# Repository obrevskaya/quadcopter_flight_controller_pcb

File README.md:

# Разработка платы контроллера полёта квадрокоптера

## Описание проекта

Проект посвящён разработке печатной платы контроллера полёта квадрокоптера в системе автоматизированного проектирования KiCad.

В рамках работы были выполнены:

* разработка структурной схемы устройства;
* выбор и обоснование элементной базы;
* разработка принципиальной электрической схемы;
* трассировка двухслойной печатной платы;
* создание трёхмерной модели печатной платы;
* подготовка производственной документации для изготовления платы.

---

## Используемая элементная база

### Микроконтроллер

**STM32F405VGTx**

* ARM Cortex-M4;
* 32-разрядная архитектура;
* обработка данных датчиков;
* формирование управляющих сигналов.

### Датчики

**ICM-20602**

* трёхосевой гироскоп;
* трёхосевой акселерометр.

**LIS3MDL**

* трёхосевой магнитометр;
* определение ориентации относительно магнитного поля Земли.

**BMP280**

* барометрический датчик давления;
* оценка высоты полёта.

### Навигация

**NEO-M8N**

* GPS/GLONASS модуль;
* определение координат и скорости движения.

### Подсистема питания

**LM7805**

* стабилизатор питания 5 В.

**AMS1117-3.3**

* стабилизатор питания 3.3 В.

---

## Разработка печатной платы

Печатная плата выполнена в системе автоматизированного проектирования **KiCad**.

Особенности реализации:

* двухслойная конструкция;
* заливка полигона земли на обоих слоях;
* разделение сигнальных и силовых цепей;
* минимизация длины соединений;
* размещение монтажных отверстий;
* подготовка Gerber-файлов для производства.

Размер платы:

```text
70 × 70 мм
```
---

## Полученные результаты

В результате работы была разработана печатная плата контроллера полёта квадрокоптера, включающая:

* структурную схему устройства;
* принципиальную электрическую схему;
* двухслойную топологию печатной платы;
* комплект производственных файлов;
* трёхмерную модель устройства.

Полученная конструкция пригодна для последующего изготовления и монтажа компонентов.

---

## Используемые инструменты

* KiCad
* Draw.io
* ARM STM32
* PCB Design
* Embedded Systems

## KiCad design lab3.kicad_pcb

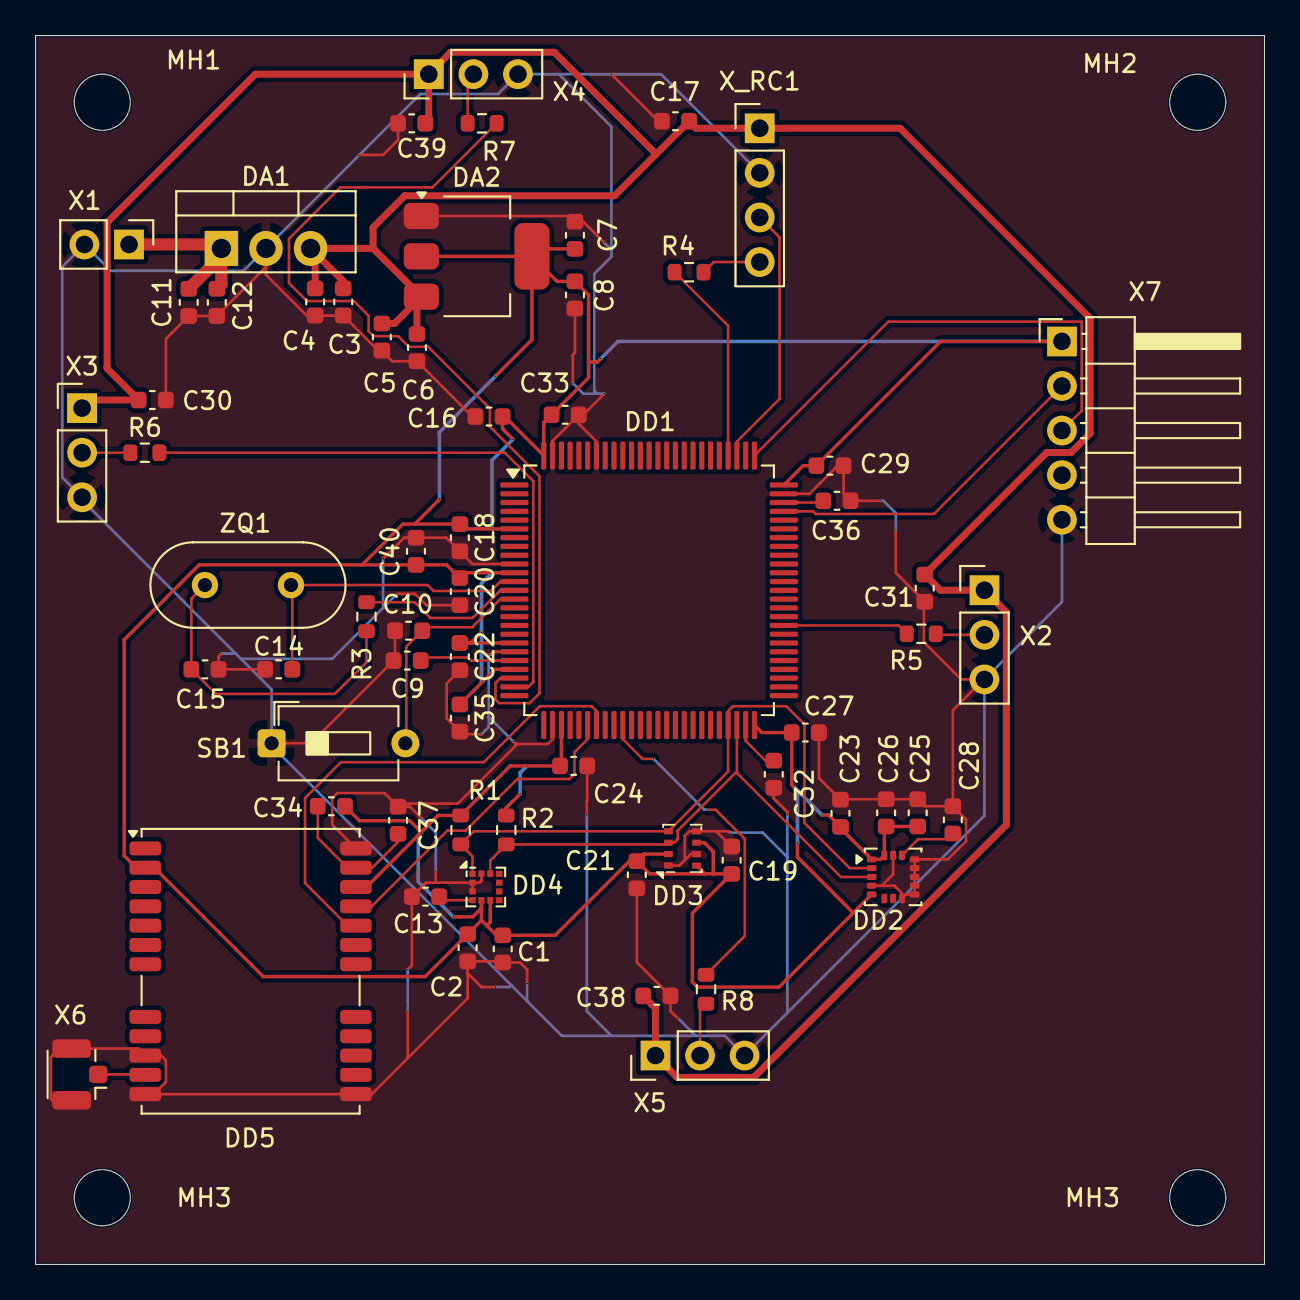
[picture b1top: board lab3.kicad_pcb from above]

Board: 2 copper layers, 70.0 x 70.0 mm, 69 parts (0 on the bottom side), 32 nets.

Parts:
C1, C3, C5, C8, C12, C13, C17, C18, C19, C20, C21, C22, C24, C25, C27, C28, C29, C30, C31, C33, C34, C35, C38, C39: 100nF; C_0603_1608Metric
C2: 1nF; C_0603_1608Metric
C4, C6, C7, C11: 10uF; C_0603_1608Metric
C9: 0.1uF; C_0603_1608Metric
C10, C16, C23: 10nF; C_0603_1608Metric
C14, C15: 30nF; C_0603_1608Metric
C26: 2.2 uF; C_0603_1608Metric
C32, C36: 2.2uF; C_0603_1608Metric
C37: 10 uF; C_0603_1608Metric
C40: 4.7uF; C_0603_1608Metric
DA1: LM7805_TO220; TO-220-3_Vertical
DA2: AMS1117-3.3; SOT-223-3_TabPin2
DD1: STM32F405VGTx; LQFP-100_14x14mm_P0.5mm
DD2: ICM-20602; LGA-16_3x3mm_P0.5mm_LayoutBorder3x5y
DD3: BMP280; Bosch_LGA-8_2x2.5mm_P0.65mm_ClockwisePinNumbering
DD4: LIS3MDL; LGA-12_2x2mm_P0.5mm
DD5: NEO-M8N; ublox_NEO
MH1, MH2, MH3, MH3#2: MountingHole_3.2mm_M3
R1, R2: 4.7k; R_0603_1608Metric
R3, R4: 100; R_0603_1608Metric
R5, R6, R7, R8: 100 Ω; R_0603_1608Metric
SB1: SW_Push; SW_DIP_SPSTx01_Slide_6.7x4.1mm_W7.62mm_P2.54mm_LowProfile
X1: Conn_01x02; PinHeader_1x02_P2.54mm_Vertical
X2, X3, X4, X5: Conn_01x03; PinHeader_1x03_P2.54mm_Vertical
X6: Conn_Coaxial; U.FL_Hirose_U.FL-R-SMT-1_Vertical
X7: Conn_01x05; PinHeader_1x05_P2.54mm_Horizontal
X_RC1: RC_RECEIVER; PinHeader_1x04_P2.54mm_Vertical
ZQ1: Crystal; Crystal_HC18-U_Vertical

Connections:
+3V3: C1.1, C2.2, C7.1, C8.1, C16.1, C18.1, C19.2, C20.1, C21.2, C22.1, C23.2, C24.1, C25.2, C26.2, C27.1, C29.1, C33.1, C34.2, C35.1, C40.2, DA2.2 (VO), DD1.6 (VBAT), DD1.11 (VDD), DD1.19 (VDD), DD1.22 (VDDA), DD1.28 (VDD), DD1.50 (VDD), DD1.75 (VDD), DD1.100 (VDD), DD2.1 (VDDIO), DD2.5 (~CS), DD2.16 (VDD), DD3.2 (CSB), DD3.6 (VDDIO), DD3.8 (VDD), DD4.5 (Vdd), DD4.6 (Vdd_IO), DD5.2 (D_SEL), DD5.22 (V_BCKP), R1.2, R2.1, X7.1
+5V: C3.1, C4.1, C5.1, C6.1, C17.1, C30.1, C31.1, C38.1, C39.1, DA1.3 (VO), DA2.3 (VI), X2.1, X3.1, X4.1, X5.1, X_RC1.1
+BATT: C11.1, C12.1, DA1.1 (VI), X1.1
GND: C1.2, C2.1, C3.2, C4.2, C5.2, C6.2, C7.2, C8.2, C9.2, C10.1, C11.2, C12.2, C13.1, C14.1, C15.1, C16.2, C17.2, C18.2, C19.1, C20.2, C21.1, C22.2, C23.1, C24.2, C25.1, C26.1, C27.2, C28.1, C29.2, C30.2, C31.2, C32.2, C33.2, C35.2, C36.2, C37.1, C38.2, C39.2, C40.1, DA1.2 (GND), DA2.1 (GND), DD1.10 (VSS), DD1.20 (VSSA), DD1.27 (VSS), DD1.74 (VSS), DD1.94 (BOOT0), DD1.99 (VSS), DD2.4 (SAO/SD0), DD2.8 (FSYNC), DD2.9 (GND), DD2.10 (GND), DD2.11 (GND), DD2.12 (GND), DD2.13 (GND), DD2.15 (GND), DD3.1 (GND), DD3.5 (SDO), DD3.7 (GND), DD4.2 (GND), DD4.3 (GND), DD4.12 (GND), DD5.10 (GND), DD5.12 (GND), DD5.13 (GND), DD5.24 (GND), SB1.1, X1.2, X2.3, X3.3, X4.3, X5.3, X6.2 (Ext), X7.5, X_RC1.2
M1_PWM: DD1.24 (PA1), R6.2
M2_PWM: DD1.35 (PB0), R8.2
M3_PWM: DD1.59 (PD12), R5.2
M4_PWM: DD1.23 (PA0), R7.2
unnamed: C15.2, R3.2, ZQ1.1
unnamed: C9.1, DD1.14 (NRST), SB1.2
unnamed: C14.2, DD1.12 (PH0), ZQ1.2
unnamed: DD1.13 (PH1), R3.1
unnamed: C32.1, DD1.49 (VCAP_1)
unnamed: C36.1, DD1.73 (VCAP_2)
unnamed: C10.2, DD1.21 (VREF+)
unnamed: C28.2, DD2.14 (REGOUT)
unnamed: C13.2, DD4.4 (C1)
unnamed: DD5.11 (RF_IN), X6.1 (In)
unnamed: C34.1, C37.2, DD5.23 (VCC)
unnamed: R5.1, X2.2
unnamed: R6.1, X3.2
unnamed: R7.1, X4.2
unnamed: R8.1, X5.2
unnamed: R4.1, X_RC1.4
RX: DD1.31 (PA6), DD5.21 (RXD/SPI_MOSI)
RX_receiver: DD1.78 (PC10), X_RC1.3
SCL: DD1.47 (PB10), DD2.2 (SCL/SPC), DD3.4 (SCK), DD4.1 (SCL/SPC), R1.1
SDA: DD1.48 (PB11), DD2.3 (SDA/SDI), DD3.3 (SDI), DD4.11 (SDA/SDI/SDO), R2.2
SWCLK: DD1.76 (PA14), X7.3
SWDIO: DD1.72 (PA13), X7.2
TX: DD1.32 (PA7), DD5.20 (TXD/SPI_MISO)
TX_receiver: DD1.79 (PC11), R4.2
